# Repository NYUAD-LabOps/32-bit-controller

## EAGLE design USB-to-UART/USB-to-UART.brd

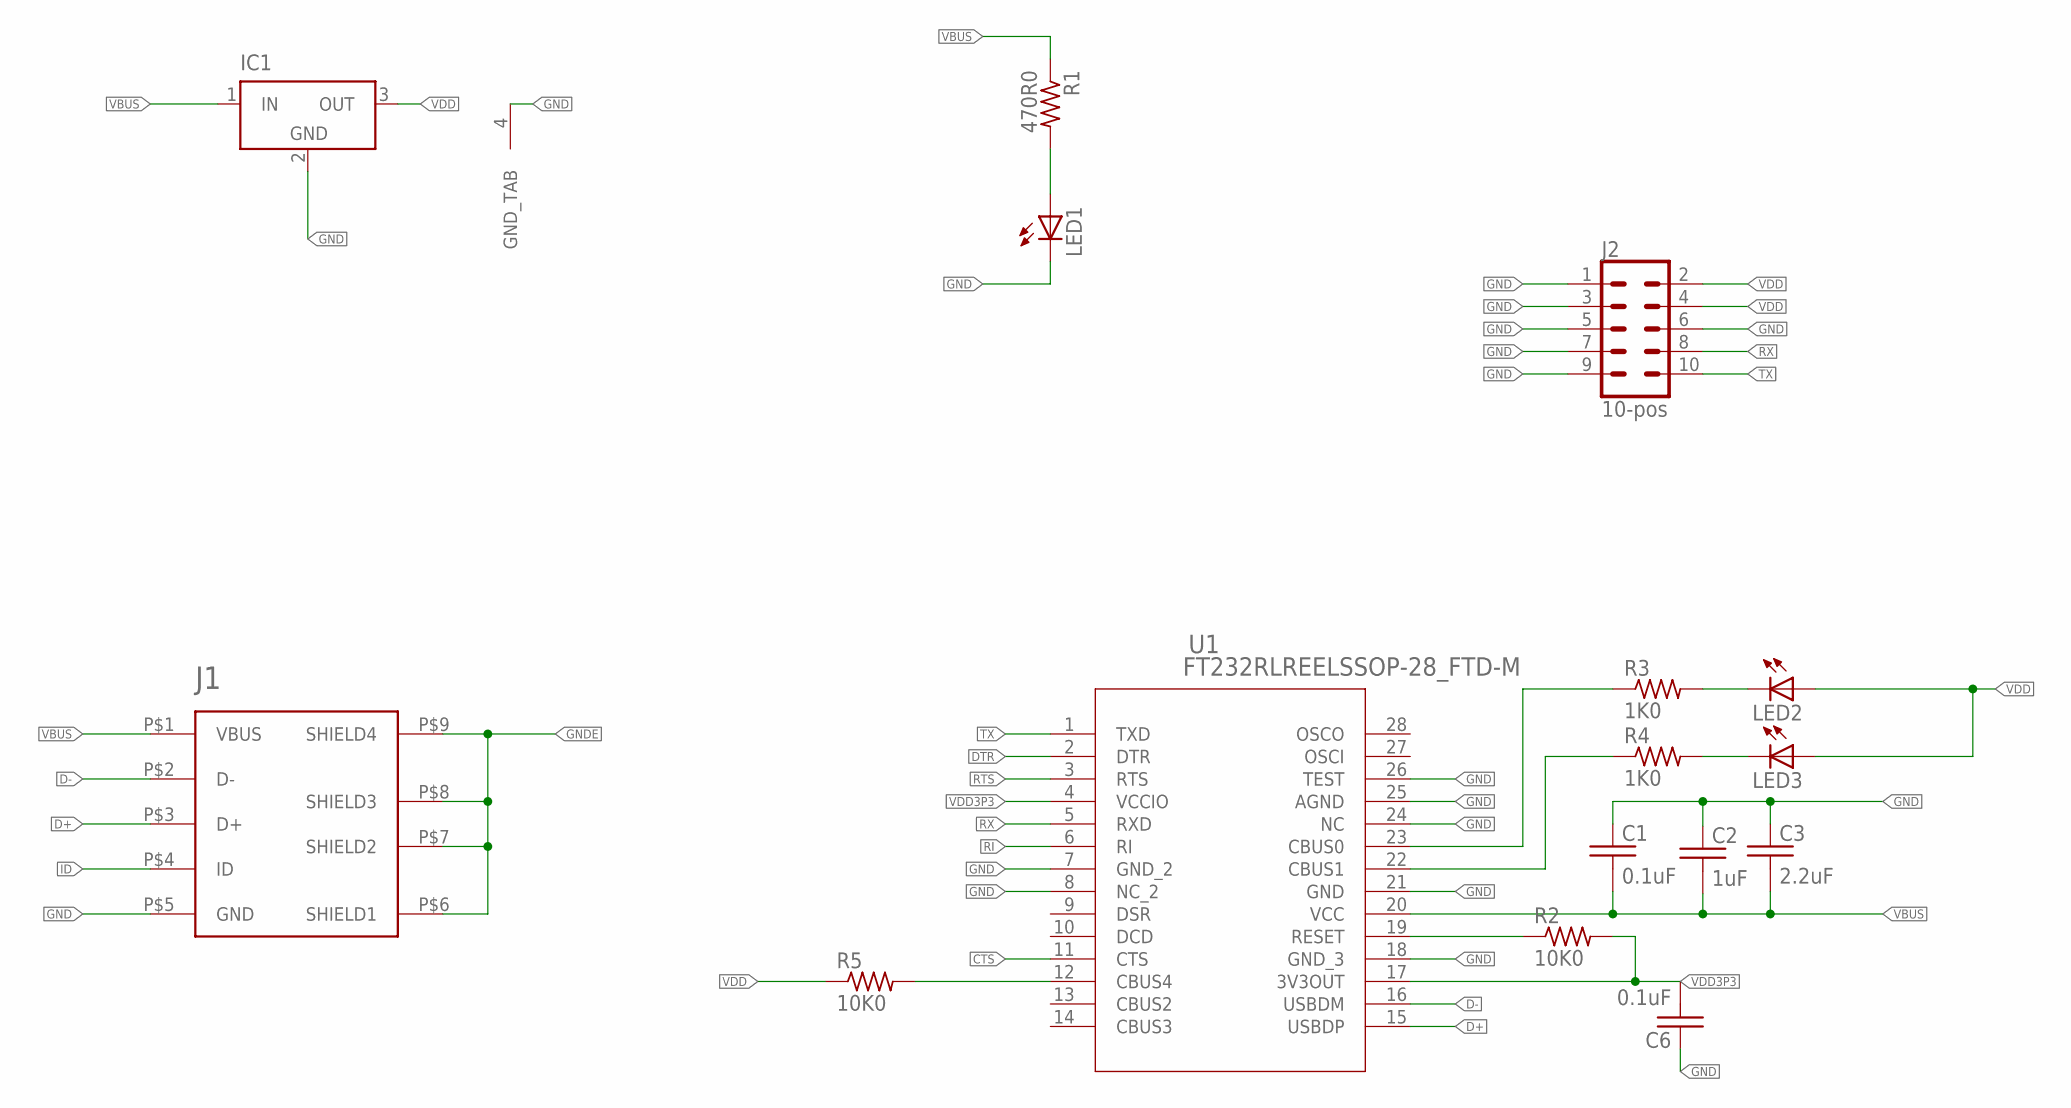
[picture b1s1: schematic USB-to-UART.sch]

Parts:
C1, C6: 0.1uF; 0402
C2: 1uF; 0402
C3: 2.2uF; 0402
IC1: LT1129CST3; SOT223
J1: USB-B-Micro; USB_MICRO-B
J2: 10-pos; 2X5
LED1, LED2, LED3: Green; LED_0805_GREEN
R1: 470R0; 0402
R2, R5: 10K0; 0402
R3, R4: 1K0; 0402
U1: FT232RLREELSSOP-28_FTD-M; SSOP-28_FTD-M

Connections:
CTS: U1.11 (CTS)
D+: J1.P$3 (D+), U1.15 (USBDP)
D-: J1.P$2 (D-), U1.16 (USBDM)
DTR: U1.2 (DTR)
GND: C1.P$1 (1), C2.P$1 (1), C3.P$1 (1), C6.P$1 (1), IC1.2 (GND), IC1.4 (GND_TAB), J1.P$5 (GND), J2.1, J2.3, J2.5, J2.6, J2.7, J2.9, LED1.C, U1.7 (GND_2), U1.8 (NC_2), U1.18 (GND_3), U1.21 (GND), U1.24 (NC), U1.25 (AGND), U1.26 (TEST)
GNDE: J1.P$6 (SHIELD1), J1.P$7 (SHIELD2), J1.P$8 (SHIELD3), J1.P$9 (SHIELD4)
ID: J1.P$4 (ID)
unnamed: LED1.A, R1.P$2 (2)
unnamed: R2.P$1 (1), U1.19 (RESET)
unnamed: R3.P$1 (1), U1.23 (CBUS0)
unnamed: LED2.C, R3.P$2 (2)
unnamed: R4.P$1 (1), U1.22 (CBUS1)
unnamed: LED3.C, R4.P$2 (2)
unnamed: R5.P$2 (2), U1.12 (CBUS4)
RI: U1.6 (RI)
RTS: U1.3 (RTS)
RX: J2.8, U1.5 (RXD)
TX: J2.10, U1.1 (TXD)
VBUS: C1.P$2 (2), C2.P$2 (2), C3.P$2 (2), IC1.1 (IN), J1.P$1 (VBUS), R1.P$1 (1), U1.20 (VCC)
VDD: IC1.3 (OUT), J2.2, J2.4, LED2.A, LED3.A, R5.P$1 (1)
VDD3P3: C6.P$2 (2), R2.P$2 (2), U1.4 (VCCIO), U1.17 (3V3OUT)

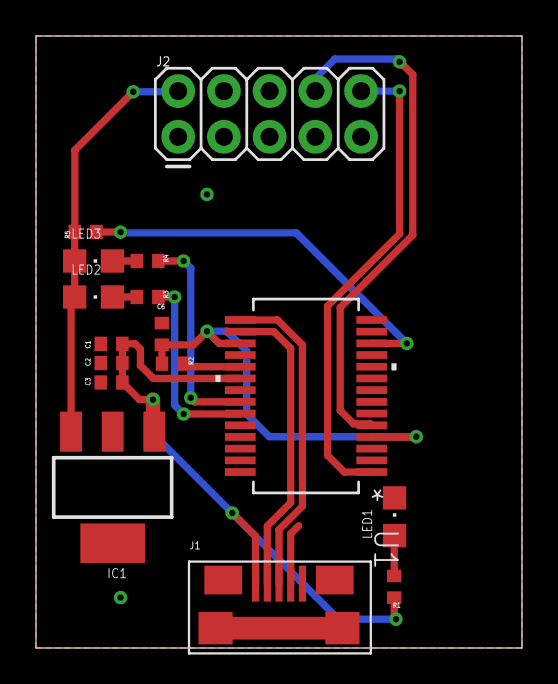
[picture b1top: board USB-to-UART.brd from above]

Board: 2 copper layers, 27.0 x 34.0 mm, 16 parts (0 on the bottom side), 16 nets.

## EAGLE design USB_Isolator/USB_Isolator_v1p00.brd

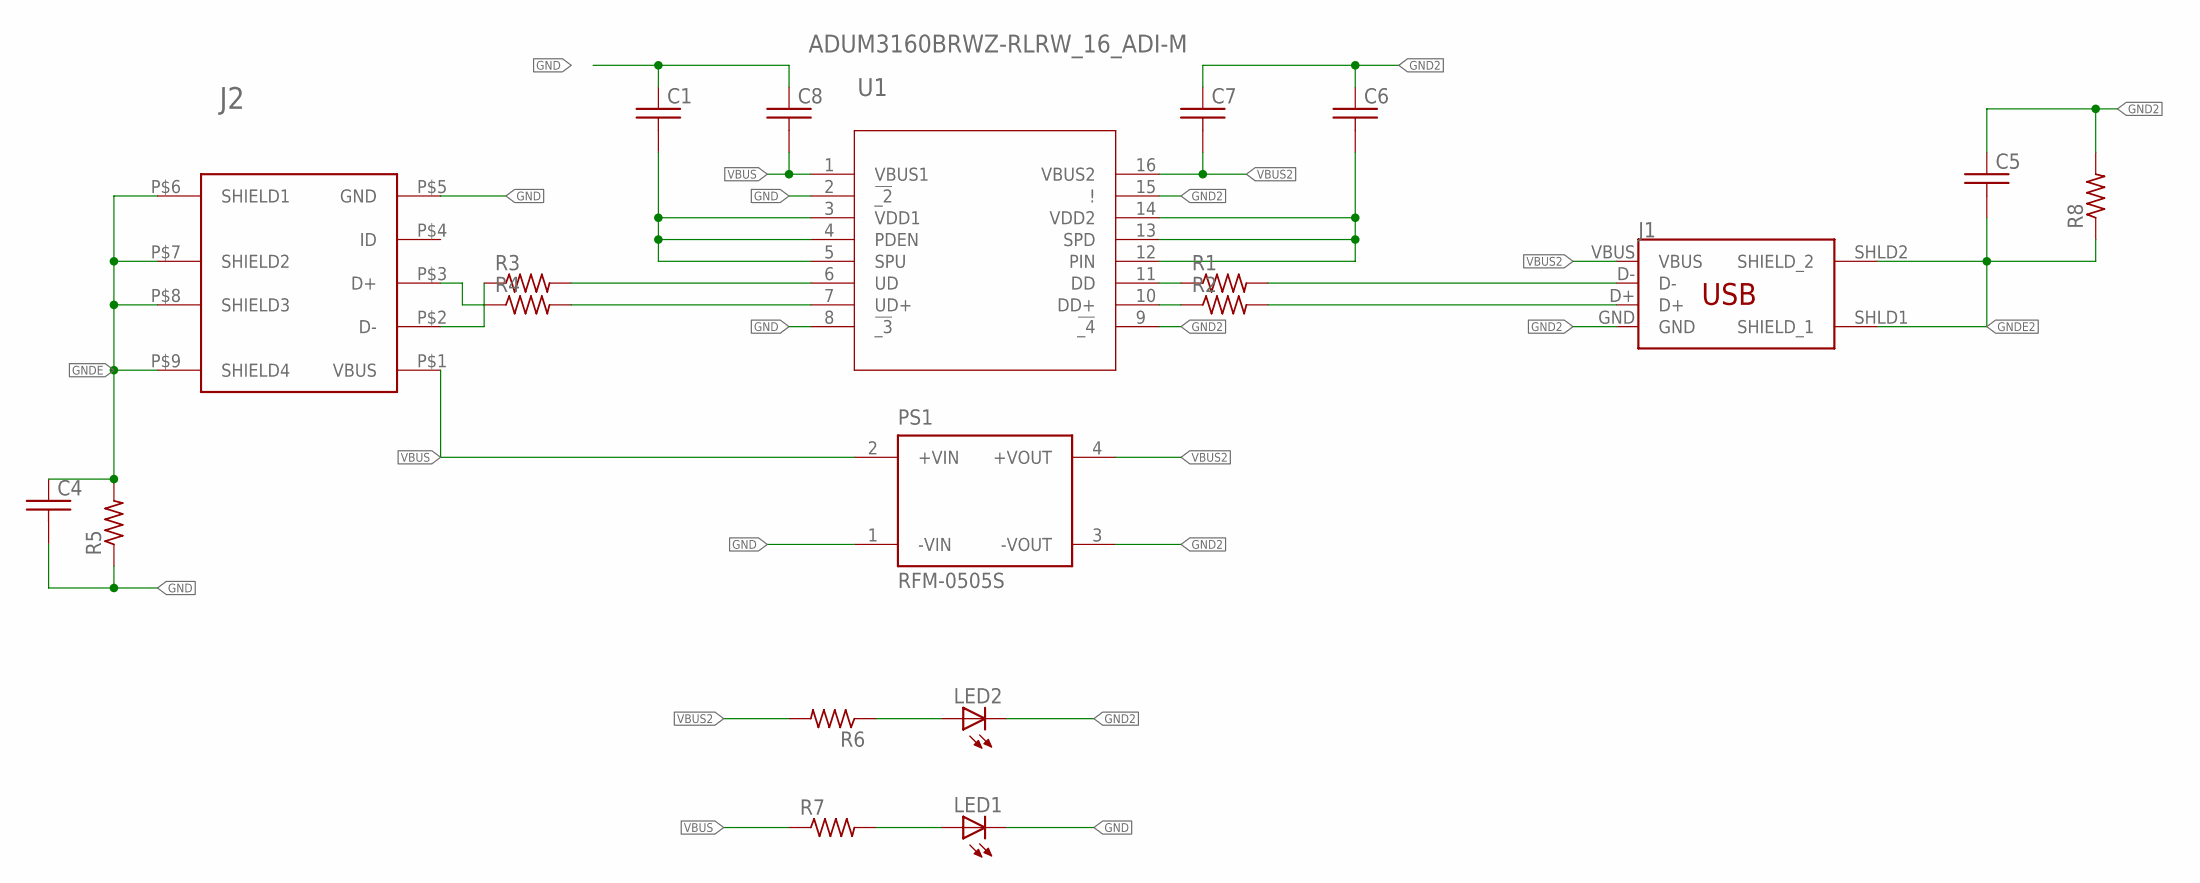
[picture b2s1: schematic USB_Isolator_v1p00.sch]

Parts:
C1, C4, C5, C6, C7, C8: C_0402; 0402
J1: USB_A; USB_A_SMT
J2: USB_MICRO-B
LED1, LED2: LED_0805_GREEN
PS1: RFM-0505S; CONV_RFM-0505S
R1, R2, R3, R4, R5, R6, R7, R8: R_0402; 0402
U1: ADUM3160BRWZ-RLRW_16_ADI-M; RW_16_ADI-M

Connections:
GND: C1.P$1 (1), C4.P$2 (2), C8.P$1 (1), J2.P$5 (GND), LED1.C, PS1.1 (-VIN), R5.P$1 (1), U1.2 (!_2), U1.8 (!_3)
GND2: C5.P$1 (1), C6.P$1 (1), C7.P$1 (1), J1.GND, LED2.C, PS1.3 (-VOUT), R8.P$2 (2), U1.9 (!_4), U1.15 (!)
GNDE: C4.P$1 (1), J2.P$6 (SHIELD1), J2.P$7 (SHIELD2), J2.P$8 (SHIELD3), J2.P$9 (SHIELD4), R5.P$2 (2)
GNDE2: C5.P$2 (2), J1.SHLD1 (SHIELD_1), J1.SHLD2 (SHIELD_2), R8.P$1 (1)
unnamed: R3.P$2 (2), U1.6 (UD)
unnamed: R4.P$2 (2), U1.7 (UD+)
unnamed: R1.P$1 (1), U1.11 (DD)
unnamed: R2.P$1 (1), U1.10 (DD+)
unnamed: J2.P$3 (D+), R4.P$1 (1)
unnamed: J2.P$2 (D-), R3.P$1 (1)
unnamed: LED2.A, R6.P$1 (1)
unnamed: J1.D+, R2.P$2 (2)
unnamed: J1.D-, R1.P$2 (2)
unnamed: C6.P$2 (2), U1.12 (PIN), U1.13 (SPD), U1.14 (VDD2)
unnamed: C1.P$2 (2), U1.3 (VDD1), U1.4 (PDEN), U1.5 (SPU)
unnamed: LED1.A, R7.P$2 (2)
VBUS: C8.P$2 (2), J2.P$1 (VBUS), PS1.2 (+VIN), R7.P$1 (1), U1.1 (VBUS1)
VBUS2: C7.P$2 (2), J1.VBUS, PS1.4 (+VOUT), R6.P$2 (2), U1.16 (VBUS2)

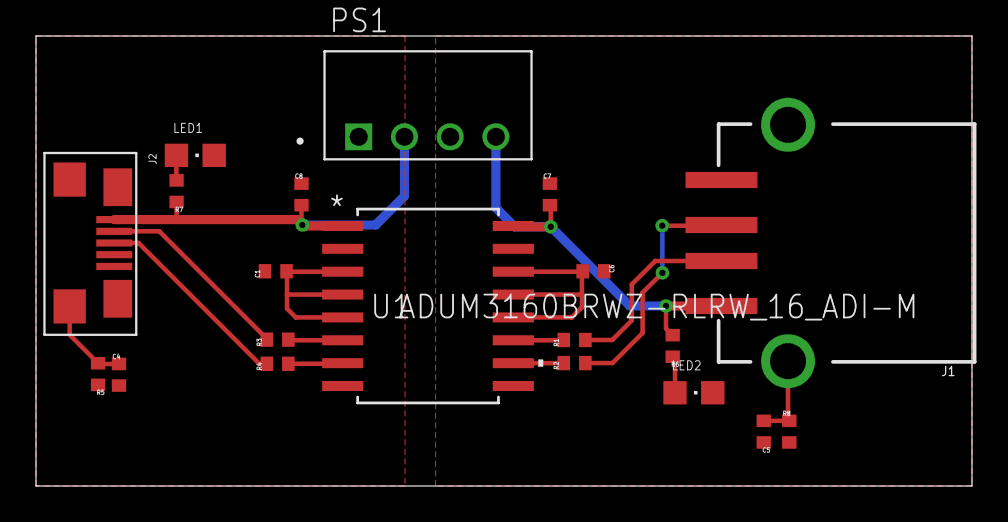
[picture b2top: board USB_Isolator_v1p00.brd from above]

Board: 2 copper layers, 52.0 x 25.0 mm, 20 parts (0 on the bottom side), 18 nets.

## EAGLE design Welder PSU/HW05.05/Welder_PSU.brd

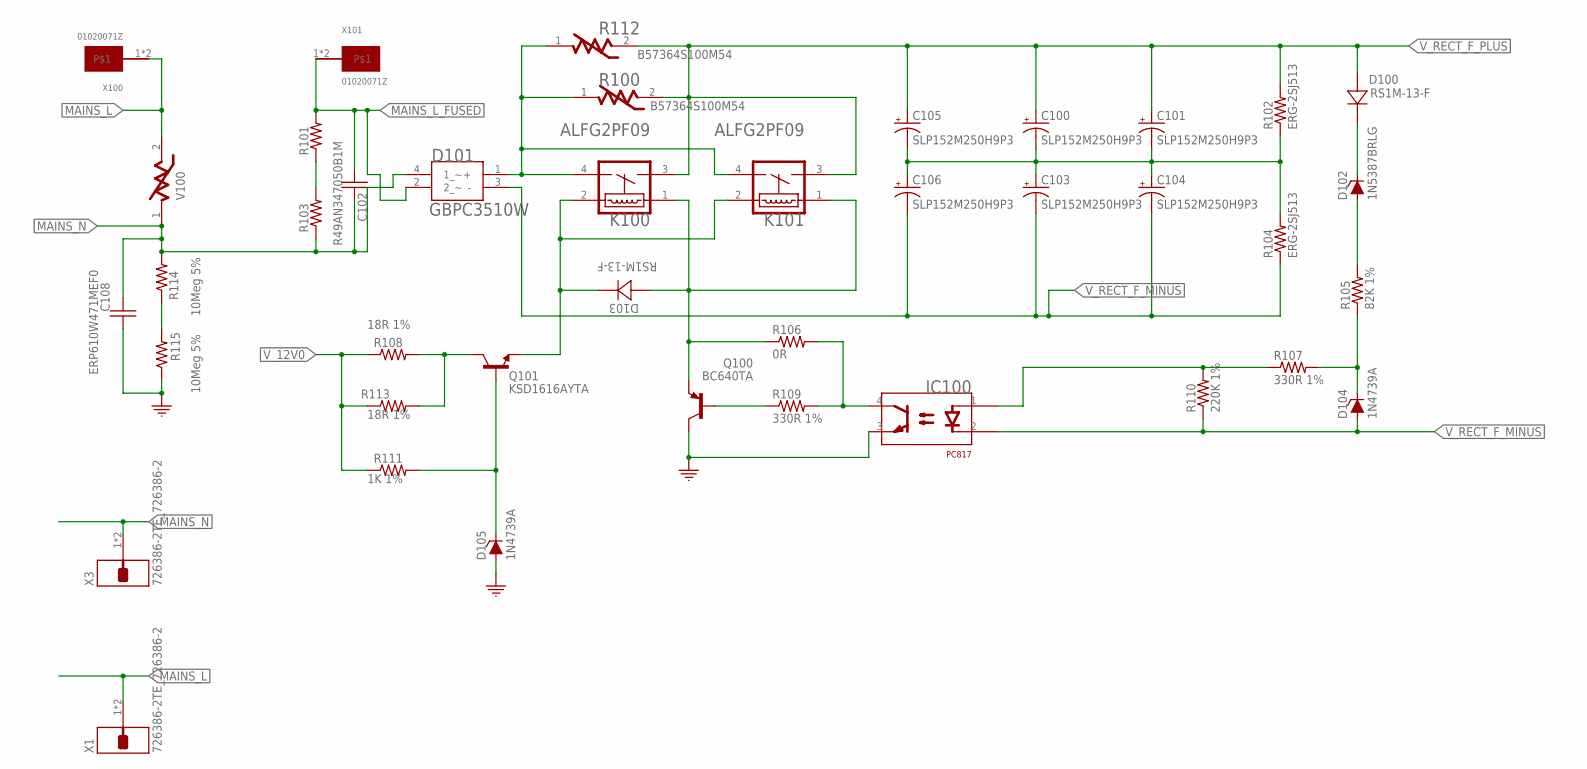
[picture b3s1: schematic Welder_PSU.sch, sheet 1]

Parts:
C100, C101, C103, C104, C105, C106: SLP152M250H9P3; CAPACITOR-ELKO-400V-RM10-35X50
C102: R49AN347050B1M
C108: ERP610W471MEF0; CAPACITOR-FILM-RM12.5MM-12MM
D100, D103: RS1M-13-F; SMA-DIODE
D101: GBPC3510W
D102: 1N5387BRLG; DO-201AD
D104, D105: 1N4739A; DO-201AD
IC100: PC817; DIP04
K100, K101: PANASONIC_ALFG2PF09PANASONIC_ALFG2PF09_0_0; PANASONIC_ALFG2PF09_0
Q100: BC640TA; TO-92
Q101: KSD1616AYTA; TO-92
R100, R112: B57364S100M54; VARISTOR_D25_P7.5
R101, R103: R_1206EIA1206; EIA1206
R102, R104: ERG-2SJ513; ERG-2S
R105: 82K 1%; R2010
R106: 0R; EIA0603
R107, R109: 330R 1%; EIA0603
R108, R113: R_2010EIA2010; EIA2010; PART_VALUE 18R 1%
R110: 220K 1%; EIA0603
R111: R_1206EIA1206; EIA1206; PART_VALUE 1K 1%
R114, R115: RNF12FTD10M0; RES-RM12.5-VR37
V100: B72205S0271K101B72205S2131K101; EPCOS_B72205S0271K101_0
X1, X3: 726386-2TE_726386-2; TE_726386-2
X100, X101: 01020071Z; FUSE_CLIP_01020071Z

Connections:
GND: C108.1, D105.A, IC100.3 (EMITTER), Q100.2 (C), R115.1; also elsewhere on the board
MAINS_L: V100.2, X1.1, X1.1-2, X100.1, X100.1-1
MAINS_L_FUSED: C102.2, D101.2 (2_~), R101.2, X101.1, X101.1-1; also elsewhere on the board
MAINS_N: C102.1, C108.2, D101.4 (1_~), R103.1, R114.2, V100.1, X3.1, X3.1-2; also elsewhere on the board
unnamed: R114.1, R115.2
unnamed: D101.1 (+), K100.4 (COM), K101.4 (COM), R100.1, R112.1
unnamed: D103.C, K100.2, K101.2, Q101.1 (E)
unnamed: R101.1, R103.2
unnamed: D103.A, K100.1, K101.1, Q100.1 (E), R106.1
unnamed: Q101.2 (C), R108.2, R113.2
unnamed: Q100.3 (B), R109.1
unnamed: D105.K (C), Q101.3 (B), R111.2
unnamed: IC100.4 (COLLECTOR), R106.2, R109.2
unnamed: C100.2 (-), C101.2 (-), C103.1 (+), C104.1 (+), C105.2 (-), C106.1 (+), R102.1, R104.2
unnamed: D104.K (C), R105.1, R107.2
unnamed: D102.A, R105.2
unnamed: D100.C, D102.K (C)
unnamed: IC100.1 (ANODE), R107.1, R110.2
V_12V0: R108.1, R111.1, R113.1; also elsewhere on the board
V_RECT_F_MINUS: C103.2 (-), C104.2 (-), C106.2 (-), D101.3 (-), D104.A, IC100.2 (CATHODE), R104.1, R110.1; also elsewhere on the board
V_RECT_F_PLUS: C100.1 (+), C101.1 (+), C105.1 (+), D100.A, K100.3 (NO), K101.3 (NO), R100.2, R102.2, R112.2; also elsewhere on the board

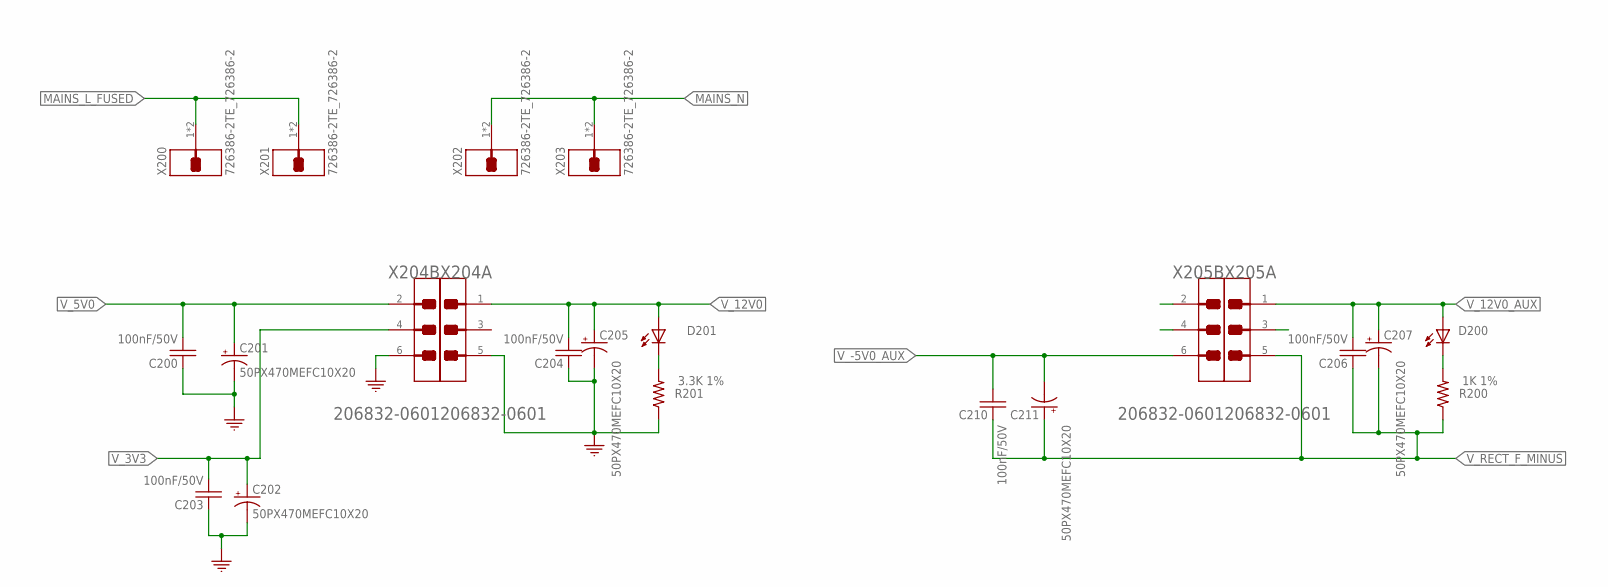
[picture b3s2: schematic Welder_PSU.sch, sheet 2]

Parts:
C200, C203, C204, C206, C210: 100nF/50V; EIA0603
C201, C202, C205, C207, C211: 50PX470MEFC10X20; CAPACITOR-ELKO-RM5-10X16
D200, D201: 26-21/GPC-F3138B/CA; SMD1206-LED
R200: 1K 1%; EIA0603
R201: 3.3K 1%; EIA0603
X200, X201, X202, X203: 726386-2TE_726386-2; TE_726386-2
X204, X205: MOLEX_206832-0601MOLEX_206832-0601; MOLEX_206832-0601

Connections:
GND: C200.1, C201.2 (-), C202.2 (-), C203.1, C204.1, C205.2 (-), R201.1, X204.5, X204.6; also elsewhere on the board
MAINS_L_FUSED: X200.1, X200.1-2, X201.1, X201.1-2; also elsewhere on the board
MAINS_N: X202.1, X202.1-2, X203.1, X203.1-2; also elsewhere on the board
unnamed: D201.2 (C), R201.2
unnamed: D200.2 (C), R200.2
V_3V3: C202.1 (+), C203.2, X204.4; also elsewhere on the board
V_5V0: C200.2, C201.1 (+), X204.2; also elsewhere on the board
V_12V0: C204.2, C205.1 (+), D201.1 (A), X204.1; also elsewhere on the board
V_12V0_AUX: C206.2, C207.1 (+), D200.1 (A), X205.1; also elsewhere on the board
V_-5V0_AUX: C210.2, C211.2 (-), X205.6; also elsewhere on the board
V_RECT_F_MINUS: C206.1, C207.2 (-), C210.1, C211.1 (+), R200.1, X205.5; also elsewhere on the board

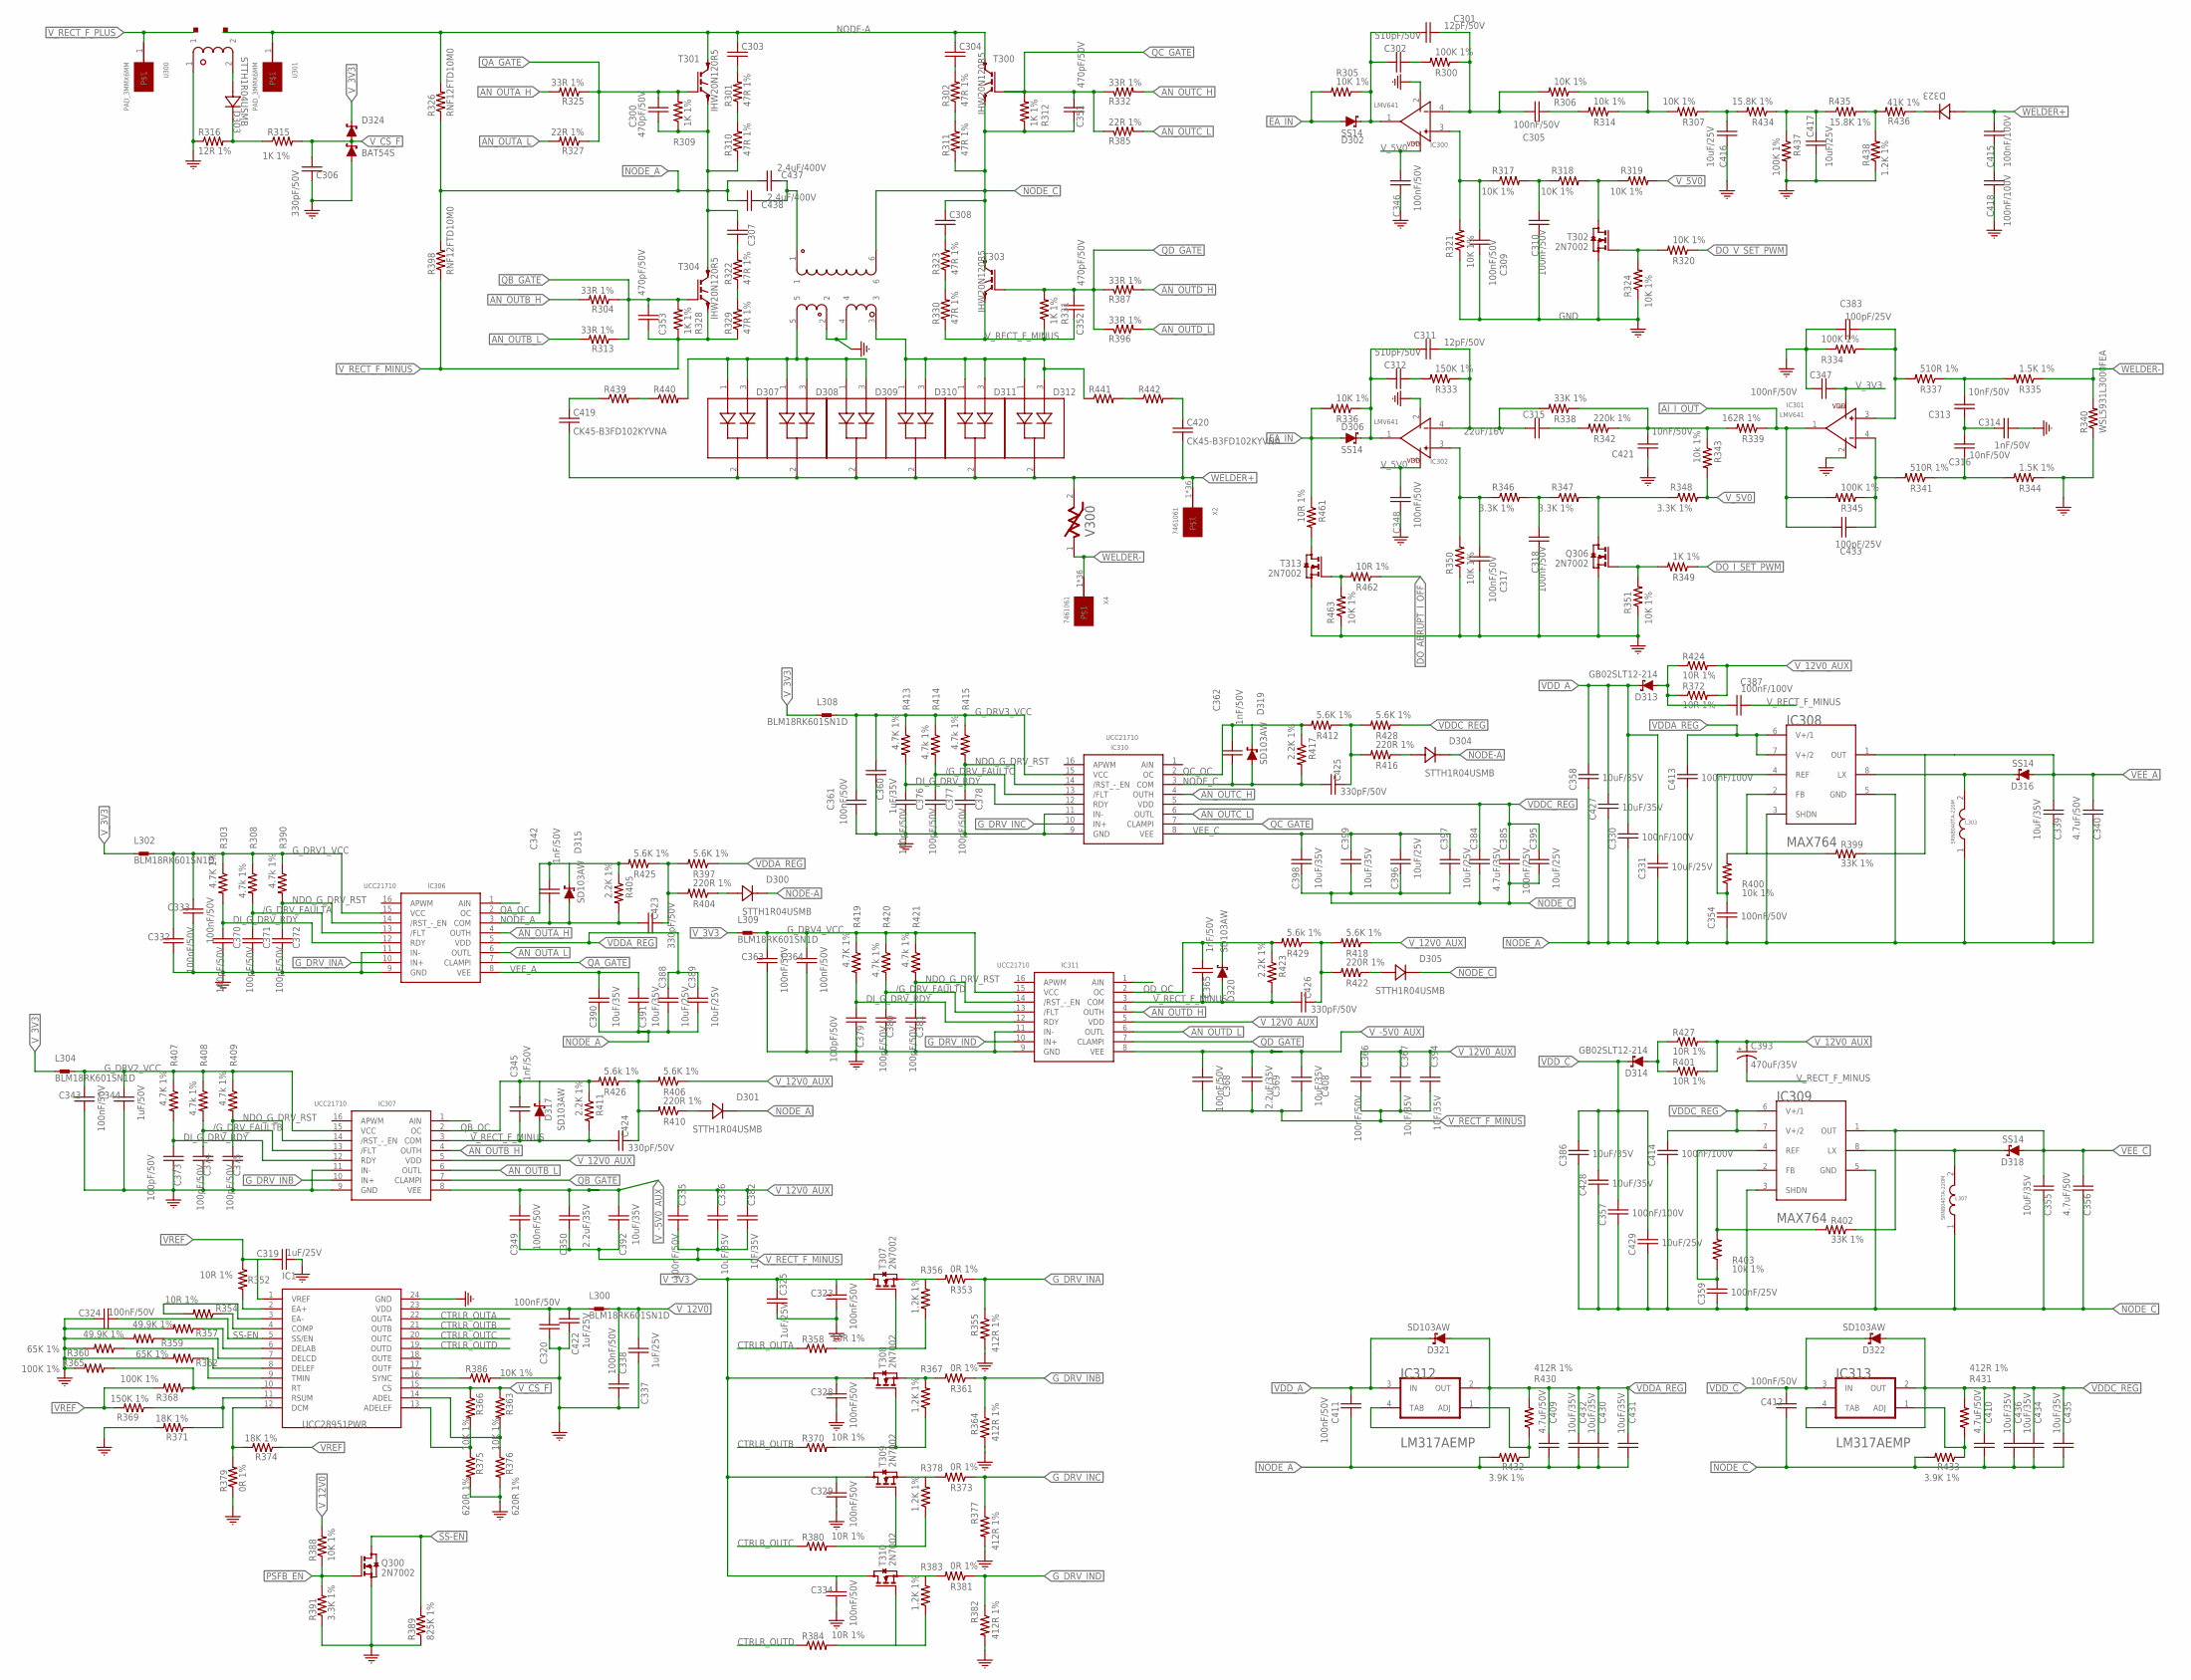
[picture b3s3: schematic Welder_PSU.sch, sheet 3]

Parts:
C300, C351, C352, C353: 470pF/50V; EIA0603
C301, C311: 12pF/50V; EIA0603
C302, C312: 510pF/50V; EIA0603
C303, C304, C307, C308: HVCC153Y6P471MEAX; CAPACITOR-FILM-RM12.5MM-12MM
C305, C309, C310, C317, C318, C320, C323, C324, C328, C329, C332, C333, C334, C335, C338, C343, C346, C347, C348, C349, C354, C361, C363, C364, C366, C368, C411, C412: 100nF/50V; EIA0603
C306, C423, C424, C425, C426: 330pF/50V; EIA0603
C313, C316, C421: 10nF/50V; EIA0603
C314, C342, C345, C362, C365: 1nF/50V; EIA0603
C315: 22uF/16V; EIA0603
C319, C325, C337, C422: 1uF/25V; EIA0603
C330, C357, C387, C413, C414, C415, C418: 100nF/100V; EIA0603
C331, C388, C389, C395, C396, C397, C416, C417, C429: 10uF/25V; EIA0603
C336, C339, C355, C358, C367, C386, C390, C391, C392, C398, C399, C408, C427, C428, C430, C431, C432, C434, C435, C436: 10uF/35V; EIA0603
C340, C356, C409, C410: 4.7uF/50V; EIA0603
C344: 1uF/50V; EIA0603
C350, C369: 2.2uF/35V; EIA0603
C359, C385: 100nF/25V; EIA0603
C360: 1uF/35V; EIA0603
C370, C371, C372, C373, C374, C375, C376, C377, C378, C379, C380, C381: 100pF/50V; EIA0603
C382, C394: 10F/35V; EIA0603
C383, C433: 100pF/25V; EIA0603
C384: 4.7uF/35V; EIA0603
C393: 470uF/35V; CAPACITOR-ELKO-RM5-10X16
C419, C420: CK45-B3FD102KYVNA; C_DISC_P7.5D12
C437, C438: ECW-F4245JLB; CAPACITOR-FILM-RM17.5-28X17.5X25
D300, D301, D303, D304, D305, D323: STTH1R04USMB; SMB
D302, D306, D316, D318: SS14; SMA
D307, D308, D309, D310, D311, D312: FEP30DP-E3/45TO-247AD; TO-247AD
D313, D314: GB02SLT12-214; SMB
D315, D317, D319, D320, D321, D322: SD103AW; SOD-323
D324: BAT54S; SOT23DUALDIODE
IC1: UCC28951PWR; TSSOP24
IC300, IC301, IC302: LMV641; SOT-23-5
IC306, IC307, IC310, IC311: UCC21710; SOIC16_WIDE_HV
IC308, IC309: MAX764CSA+; SOIC8
IC312, IC313: LM317AEMP; SOT223_LM317AEMP
L300, L302, L304, L308, L309: BLM18RK601SN1D; 0603
L303, L307: SRN8040TA-220M
Q300, Q306: 2N7002; SOT23
R300, R334, R345, R365, R368, R437: 100K 1%; EIA0603
R301, R302, R310, R311, R322, R323, R329, R330: 47R 1%; R2512
R303, R407, R413, R419: 4.7K 1%; EIA0603
R304, R313, R325, R332, R387, R396: 33R 1%; EIA2010
R305, R306, R307, R317, R318, R319, R320, R321, R324, R336, R350, R351, R363, R366, R386, R388, R463: 10K 1%; EIA0603
R308, R390, R408, R409, R414, R415, R420, R421: 4.7k 1%; EIA0603
R309, R312, R328, R331: 1K 1%; EIA2010
R314, R343, R400, R403: 10k 1%; EIA0603
R315, R349: 1K 1%; EIA0603
R316: 12R 1%; EIA2512
R326, R398: RNF12FTD10M0; RES-RM12.5-VR37
R327, R385: 22R 1%; EIA2010
R333, R369: 150K 1%; EIA0603
R335, R344: 1.5K 1%; EIA0603
R337, R341: 510R 1%; EIA0603
R338, R399, R402: 33K 1%; EIA0603
R339: 162R 1%; EIA0603
R340: WSL5931L3000FEA; WSLP3921
R342: 220k 1%; EIA0603
R346, R347, R348, R391: 3.3K 1%; EIA0603
R352, R354, R358, R370, R380, R384, R461, R462: 10R 1%; EIA0603
R353, R361, R373, R379, R381: 0R 1%; EIA0603
R355, R364, R377, R382, R430, R431: 412R 1%; EIA0603
R356, R367, R378, R383: 1.2K 1%; EIA0603
R357, R359: 49.9K 1%; EIA0603
R360, R362: 65K 1%; EIA0603
R371, R374: 18K 1%; EIA0603
R372, R401, R424, R427: 10R 1%; EIA2512
R375, R376: 620R 1%; EIA0603
R389: 825K 1%; EIA0603
R397, R406, R412, R418, R425, R428: 5.6K 1%; EIA0603
R404, R410, R416, R422: 220R 1%; EIA0603
R405, R411, R417, R423: 2.2K 1%; EIA0603
R426, R429: 5.6k 1%; EIA0603
R432, R433: 3.9K 1%; EIA0603
R434, R435: 15.8K 1%; EIA0603
R436: 41K 1%; EIA2010
R438: 1.2K 1%; EIA2010
R439, R440, R441, R442: RR02J22RTB; RES-RM15-RSF1W
T300, T301, T303, T304: IHW20N120R5; TO-247AC
T302, T307, T308, T309, T310, T313: 2N7002; SOT23
TR300: CST206-2A
TR305: 11-0060-A
U300, U301: PAD_3MMX6MM; PAD-3.0X6.0MM
V300: B72205S0271K101B72205S2131K101; EPCOS_B72205S0271K101_0
X2, X4: 7461061; X01_M10_7461061

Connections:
/G_DRV_FAULTA: C371.2, IC306.13 (/FLT), R308.2; also elsewhere on the board
/G_DRV_FAULTB: C374.2, IC307.13 (/FLT), R408.2; also elsewhere on the board
/G_DRV_FAULTC: C377.2, IC310.13 (/FLT), R414.2; also elsewhere on the board
/G_DRV_FAULTD: C380.2, IC311.13 (/FLT), R420.2; also elsewhere on the board
AI_I_OUT: C433.2, IC301.1 (OUT), R339.1, R345.2; also elsewhere on the board
AN_OUTA_H: IC306.4 (OUTH), R325.2
AN_OUTA_L: IC306.6 (OUTL), R327.2
AN_OUTB_H: IC307.4 (OUTH), R304.2
AN_OUTB_L: IC307.6 (OUTL), R313.2
AN_OUTC_H: IC310.4 (OUTH), R332.2
AN_OUTC_L: IC310.6 (OUTL), R385.2
AN_OUTD_H: IC311.4 (OUTH), R387.2
AN_OUTD_L: IC311.6 (OUTL), R396.2
CTRLR_OUTA: IC1.22 (OUTA), R358.1
CTRLR_OUTB: IC1.21 (OUTB), R370.1
CTRLR_OUTC: IC1.20 (OUTC), R380.1
CTRLR_OUTD: IC1.19 (OUTD), R384.1
DI_G_DRV_RDY: C370.2, C373.2, C376.2, C379.2, IC306.12 (RDY), IC307.12 (RDY), IC310.12 (RDY), IC311.12 (RDY), R303.2, R407.2, R413.2, R419.2; also elsewhere on the board
DO_ABRUPT_I_OFF: R462.1; also elsewhere on the board
DO_I_SET_PWM: R349.1; also elsewhere on the board
DO_V_SET_PWM: R320.1; also elsewhere on the board
EA_IN: D302.2 (A), D306.2 (A), R305.2, R336.2, R461.1
GND: C306.1, C309.2, C310.2, C314.2, C317.2, C318.2, C319.2, C320.1, C323.1, C324.1, C325.2, C328.1, C329.1, C332.1, C333.1, C334.1, C337.2, C338.1, C343.1, C344.1, C346.2, C347.2, C348.2, C360.1, C361.1, C363.1, C364.1, C370.1, C371.1, C372.1, C373.1, C374.1, C375.1, C376.1, C377.1, C378.1, C379.1, C380.1, C381.1, C383.1, C416.2, C417.2, C418.2, C421.1, C422.2, D324.1 (A1), IC1.24 (GND), IC300.2 (VEE), IC301.2 (VEE), IC302.2 (VEE), IC306.9 (GND), IC306.11 (IN-), IC307.9 (GND), IC307.11 (IN-), IC310.9 (GND), IC310.11 (IN-), IC311.9 (GND), IC311.11 (IN-), Q300.2 (S), Q306.2 (S), R316.1, R321.1, R324.1, R334.2, R340.1, R344.1, R350.1, R351.1, R355.2, R357.2, R359.2, R360.2, R362.2, R364.2, R365.2, R371.2, R375.2, R376.2, R377.2, R379.1, R382.2, R386.2, R389.1, R391.1, R437.2, R438.1, R463.1, T302.2 (S), T313.2 (S), TR300.1, TR305.2, TR305.4; also elsewhere on the board
G_DRV1_VCC: C332.2, C333.2, IC306.15 (VCC), L302.2, R303.1, R308.1, R390.1
G_DRV2_VCC: C343.2, C344.2, IC307.15 (VCC), L304.2, R407.1, R408.1, R409.1
G_DRV3_VCC: C360.2, C361.2, IC310.15 (VCC), L308.2, R413.1, R414.1, R415.1
G_DRV4_VCC: C363.2, C364.2, IC311.15 (VCC), L309.2, R419.1, R420.1, R421.1
G_DRV_INA: IC306.10 (IN+), R353.1, R355.1
G_DRV_INB: IC307.10 (IN+), R361.1, R364.1
G_DRV_INC: IC310.10 (IN+), R373.1, R377.1
G_DRV_IND: IC311.10 (IN+), R381.1, R382.1
unnamed: C311.1, C315.2, IC302.4 (IN-), R333.1, R338.2
unnamed: IC1.12 (DCM), R374.2, R379.2
unnamed: IC1.11 (RSUM), R369.1, R371.1
unnamed: IC1.10 (RT), R365.1, R368.1
unnamed: IC1.9 (TMIN), R362.1
unnamed: IC1.8 (DELEF), R360.1
unnamed: IC1.6 (DELAB), R357.1
unnamed: IC1.7 (DELCD), R359.1
unnamed: IC1.4 (COMP), R354.1
unnamed: IC1.3 (EA-), R354.2
unnamed: IC1.2 (EA+), R352.2
unnamed: C320.2, C422.1, IC1.23 (VDD), L300.1
unnamed: IC1.16 (SYNC), R386.1
unnamed: D303.K (C), R315.1, R316.2
unnamed: R356.1, R358.2, T307.1 (G)
unnamed: IC1.13 (ADELEF), R366.2, R375.1
unnamed: R353.2, R356.2, T307.2 (S)
unnamed: IC1.14 (ADEL), R363.2, R376.1
unnamed: C421.2, R338.1, R339.2, R342.1, R343.1
unnamed: D303.A, TR300.2
unnamed: R378.1, R380.2, T309.1 (G)
unnamed: R373.2, R378.2, T309.2 (S)
unnamed: C313.2, R335.2, R337.1
unnamed: C313.1, C314.1, C316.2
unnamed: C316.1, R341.1, R344.2
unnamed: R367.1, R370.2, T308.1 (G)
unnamed: R361.2, R367.2, T308.2 (S)
unnamed: R323.1, R330.2
unnamed: C433.1, IC301.4 (IN-), R341.2, R345.1
unnamed: Q306.1 (G), R349.2, R351.2
unnamed: C383.2, IC301.3 (IN+), R334.1, R337.2
unnamed: R383.1, R384.2, T310.1 (G)
unnamed: R301.1, R310.2
unnamed: R381.2, R383.2, T310.2 (S)
unnamed: C303.2, R301.2
unnamed: C315.1, R342.2
unnamed: R462.2, R463.2, T313.1 (G)
unnamed: Q306.3 (D), R347.2, R348.1
unnamed: R302.1, R311.2
unnamed: C304.2, R302.2
unnamed: R322.1, R329.2
unnamed: C307.2, R322.2
unnamed: C308.2, R323.2
unnamed: C318.1, R346.2, R347.1
unnamed: C437.2, C438.2, TR305.1
unnamed: D310.1, D310.3, D311.1, D311.3, D312.1, D312.3, R441.1, TR305.3
unnamed: D307.1, D307.3, D308.1, D308.3, D309.1, D309.3, R440.2, TR305.5
unnamed: R439.2, R440.1
unnamed: C419.1, R439.1
unnamed: C420.1, R442.2
unnamed: R441.2, R442.1
unnamed: D314.A, R401.1, R427.1
unnamed: C317.1, IC302.3 (IN+), R346.1, R350.2
unnamed: IC309.2 (FB), R402.2, R403.2
unnamed: C423.2, R397.2, R404.2, R425.1
unnamed: IC312.1 (ADJ), R430.1, R432.1
unnamed: C359.1, IC309.4 (REF), R403.1
unnamed: IC313.1 (ADJ), R431.1, R433.1
unnamed: D318.1 (C), IC309.8 (LX), L307.2
unnamed: D316.1 (C), IC308.8 (LX), L303.2
unnamed: C354.1, IC308.4 (REF), R400.1
unnamed: IC308.2 (FB), R399.2, R400.2
unnamed: D300.A, R404.1
unnamed: C424.2, R406.2, R410.2, R426.1
unnamed: C387.1, D313.A, R372.1, R424.1
unnamed: C425.2, R412.1, R416.2, R428.2
unnamed: D304.A, R416.1
unnamed: D301.A, R410.1
unnamed: C312.1, R333.2
unnamed: R306.1, R307.2, R314.1
unnamed: R461.2, T313.3 (D)
unnamed: C311.2, C312.2, D306.1 (C), IC302.1 (OUT), R336.1
unnamed: C305.1, R314.2
unnamed: R320.2, R324.2, T302.1 (G)
unnamed: R318.2, R319.1, T302.3 (D)
unnamed: C310.1, R317.2, R318.1
unnamed: C309.1, IC300.3 (IN+), R317.1, R321.2
unnamed: C426.2, R418.2, R422.2, R429.1
unnamed: D305.A, R422.1
unnamed: C301.1, C305.2, IC300.4 (IN-), R300.1, R306.2
unnamed: C302.1, R300.2
unnamed: C301.2, C302.2, D302.1 (C), IC300.1 (OUT), R305.1
unnamed: C416.1, R307.1, R434.2
unnamed: C417.1, R434.1, R435.1, R437.1
unnamed: R435.2, R436.2, R438.2
unnamed: D323.K (C), R436.1
unnamed: C415.2, C418.1
NDO_G_DRV_RST: C372.2, C375.2, C378.2, C381.2, IC306.14 (/RST_-_EN), IC307.14 (/RST_-_EN), IC310.14 (/RST_-_EN), IC311.14 (/RST_-_EN), R390.2, R409.2, R415.2, R421.2; also elsewhere on the board
NODE-A: C303.1, C304.1, D300.K (C), D304.K (C), R326.2, T300.2 (D), T301.2 (D), U301.1
NODE_A: C300.1, C307.1, C330.2, C331.2, C339.1, C340.1, C342.1, C354.2, C358.2, C388.1, C389.1, C390.1, C391.1, C409.1, C411.1, C413.2, C423.1, C427.2, C430.1, C431.1, C432.1, C437.1, C438.1, D301.K (C), D315.A, IC306.3 (COM), IC308.3 (SHDN), IC308.5 (GND), L303.1, R309.1, R310.1, R326.1, R398.2, R405.2, R432.2, T301.3 (S), T304.2 (D)
NODE_C: C308.1, C351.1, C355.1, C356.1, C357.2, C359.2, C362.1, C384.1, C385.1, C386.2, C395.1, C396.1, C397.1, C398.1, C399.1, C410.1, C412.1, C414.2, C425.1, C428.2, C429.2, C434.1, C435.1, C436.1, D305.K (C), D319.A, IC309.3 (SHDN), IC309.5 (GND), IC310.3 (COM), L307.1, R311.1, R312.1, R417.2, R433.2, T300.3 (S), T303.2 (D), TR305.6
PSFB_EN: Q300.1 (G), R388.1, R391.2; also elsewhere on the board
QA_GATE: C300.2, IC306.7 (CLAMPI), R309.2, R325.1, R327.1, T301.1 (G)
QA_OC: C342.2, D315.C, IC306.2 (OC), R405.1, R425.2
QB_GATE: C353.2, IC307.7 (CLAMPI), R304.1, R313.1, R328.2, T304.1 (G)
QB_OC: C345.2, D317.C, IC307.2 (OC), R411.1, R426.2
QC_GATE: C351.2, IC310.7 (CLAMPI), R312.2, R332.1, R385.1, T300.1 (G)
QC_OC: C362.2, D319.C, IC310.2 (OC), R412.2, R417.1
QD_GATE: C352.2, IC311.7 (CLAMPI), R331.2, R387.1, R396.1, T303.1 (G)
QD_OC: C365.2, D320.C, IC311.2 (OC), R423.1, R429.2
SS-EN: C324.2, IC1.5 (SS/EN), Q300.3 (D), R389.2
VDDA_REG: C388.2, C389.2, C409.2, C413.1, C430.2, C431.2, C432.2, D321.A, IC306.5 (VDD), IC308.6 (V+/1), IC308.7 (V+/2), IC312.2 (OUT), IC312.4 (TAB), R397.1, R430.2
VDDC_REG: C384.2, C385.2, C395.2, C410.2, C414.1, C434.2, C435.2, C436.2, D322.A, IC309.6 (V+/1), IC309.7 (V+/2), IC310.5 (VDD), IC313.2 (OUT), IC313.4 (TAB), R428.1, R431.2
VDD_A: C330.1, C331.1, C358.1, C411.2, C427.1, D313.K (C), D321.C, IC312.3 (IN)
VDD_C: C357.1, C386.1, C412.2, C428.1, C429.1, D314.K (C), D322.C, IC313.3 (IN)
VEE_A: C339.2, C340.2, C390.2, C391.2, D316.2 (A), IC306.8 (VEE), IC308.1 (OUT), R399.1
VEE_C: C355.2, C356.2, C396.2, C397.2, C398.2, C399.2, D318.2 (A), IC309.1 (OUT), IC310.8 (VEE), R402.1
VREF: C319.1, IC1.1 (VREF), R352.1, R368.2, R369.2, R374.1
V_3V3: C323.2, C325.1, C328.2, C329.2, C334.2, C347.1, D324.2 (C2), IC301.5 (VCC), L302.1, L304.1, L308.1, L309.1, T307.3 (D), T308.3 (D), T309.3 (D), T310.3 (D); also elsewhere on the board
V_5V0: C346.1, C348.1, IC300.5 (VCC), IC302.5 (VCC), R319.2, R343.2, R348.2; also elsewhere on the board
V_12V0: C337.1, C338.2, L300.2, R388.2; also elsewhere on the board
V_12V0_AUX: C335.2, C336.2, C366.2, C367.2, C382.2, C393.1 (+), C394.2, IC307.5 (VDD), IC311.5 (VDD), R372.2, R401.2, R406.1, R418.1, R424.2, R427.2; also elsewhere on the board
V_-5V0_AUX: C349.2, C350.2, C368.2, C369.2, C392.2, C408.2, IC307.8 (VEE), IC311.8 (VEE); also elsewhere on the board
V_CS_F: C306.2, D324.3 (C1_A2), IC1.15 (CS), R315.2, R363.1, R366.1
V_RECT_F_MINUS: C335.1, C336.1, C345.1, C349.1, C350.1, C352.1, C353.1, C365.1, C366.1, C367.1, C368.1, C369.1, C382.1, C387.2, C392.1, C393.2 (-), C394.1, C408.1, C424.1, C426.1, D317.A, D320.A, IC307.3 (COM), IC311.3 (COM), R328.1, R329.1, R330.1, R331.1, R398.1, R411.2, R423.2, T303.3 (S), T304.3 (S); also elsewhere on the board
V_RECT_F_PLUS: U300.1; also elsewhere on the board
WELDER+: C415.1, C419.2, C420.2, D307.2, D308.2, D309.2, D310.2, D311.2, D312.2, D323.A, V300.2, X2.1, X2.1-1, X2.1-2, X2.1-3, X2.1-4, X2.1-5, X2.1-6, X2.1-7, X2.1-8, X2.1-9, X2.1-10, X2.1-11, X2.1-12, X2.1-13, X2.1-14, X2.1-15, X2.1-16, X2.1-17, X2.1-18, X2.1-19, X2.1-20, X2.1-21, X2.1-22, X2.1-23, X2.1-24, X2.1-25, X2.1-26, X2.1-27, X2.1-28, X2.1-29, X2.1-30, X2.1-31, X2.1-32, X2.1-33, X2.1-34, X2.1-35
WELDER-: R335.1, R340.2, V300.1, X4.1, X4.1-1, X4.1-2, X4.1-3, X4.1-4, X4.1-5, X4.1-6, X4.1-7, X4.1-8, X4.1-9, X4.1-10, X4.1-11, X4.1-12, X4.1-13, X4.1-14, X4.1-15, X4.1-16, X4.1-17, X4.1-18, X4.1-19, X4.1-20, X4.1-21, X4.1-22, X4.1-23, X4.1-24, X4.1-25, X4.1-26, X4.1-27, X4.1-28, X4.1-29, X4.1-30, X4.1-31, X4.1-32, X4.1-33, X4.1-34, X4.1-35

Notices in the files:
parts and their libraries:
COPYRIGHT: Copyright (C) 2018 Accelerated Designs. All rights reserved
Labops_Lib_AH: COPYRIGHT: Copyright (C) 2022 Ultra Librarian. All rights reserved.
